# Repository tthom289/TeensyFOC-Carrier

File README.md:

# TeensyFOC-Carrier

Teensy 4.0 + SimpleFOC carrier board for brushless motor control in a rotating LiDAR SLAM platform. Designed for the [Subterranean Systems](https://youtube.com/@subterraneansystems) VLP-16 scanner — integrates AS5600 magnetic encoder, slip ring passthrough, and GT2 belt drive motor driver circuitry on a compact custom PCB.

---

## Overview

This board eliminates the wiring mess of a breadboarded SimpleFOC setup by consolidating the Teensy 4.0, motor driver interface, and encoder connections onto a single PCB. Designed specifically for the rotating LiDAR scanner in the Subterranean Systems cave mapping platform.

**Key features:**
- Teensy 4.0 footprint with all relevant I/O broken out
- SimpleFOC-compatible motor driver header
- AS5600 magnetic encoder interface (I2C)
- JST-XHP connectors for motor phase and power leads
- Slip ring wiring passthrough support
- Designed in KiCad

---

## Bill of Materials (Connectors)

| Component | Link |
|---|---|
| Single Row 2.54mm Headers | [Amazon](https://amzn.to/3Nf74dT) |
| JST-XHP Connector Kit | [Amazon](https://amzn.to/4dmR5oD) |

---

## Related

- [Subterranean Systems YouTube](https://youtube.com/9nl) — build videos for this platform
- [SimpleFOC](https://simplefoc.com/) — motor control library

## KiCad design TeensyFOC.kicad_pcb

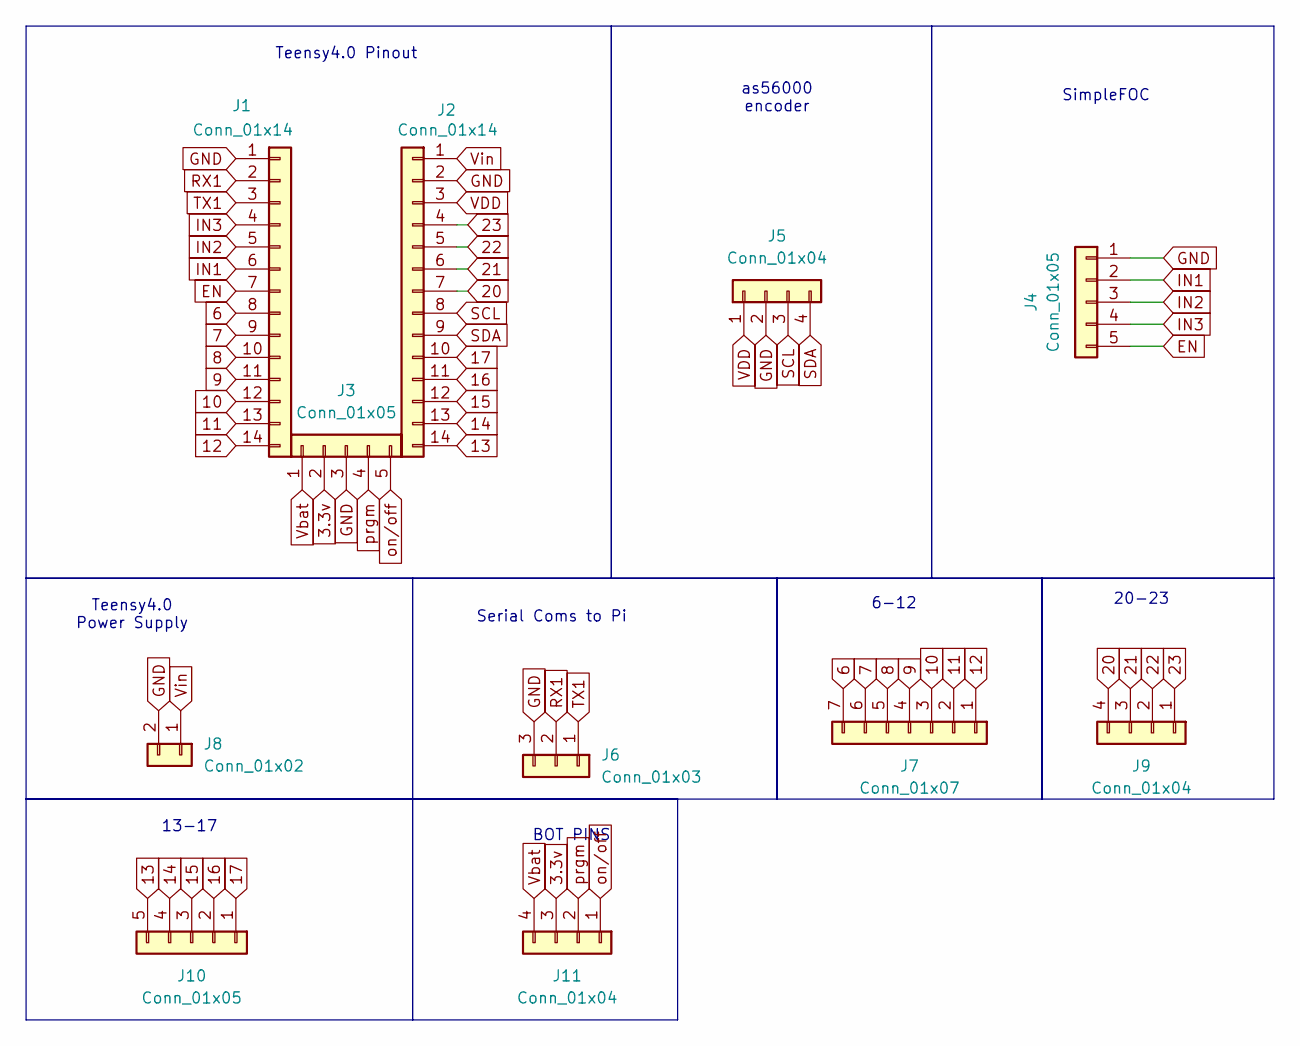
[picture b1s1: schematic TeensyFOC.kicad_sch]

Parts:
J1, J2: Conn_01x14; PinSocket_1x14_P2.54mm_Vertical
J3, J4, J10: Conn_01x05; PinSocket_1x05_P2.54mm_Vertical
J5: Conn_01x04; JST_XH_B4B-XH-A_1x04_P2.50mm_Vertical
J6: Conn_01x03; JST_XH_B3B-XH-A_1x03_P2.50mm_Vertical
J7: Conn_01x07; PinSocket_1x07_P2.54mm_Vertical
J8: Conn_01x02; JST_XH_B2B-XH-A_1x02_P2.50mm_Vertical
J9, J11: Conn_01x04; PinSocket_1x04_P2.54mm_Vertical

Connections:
3.3v: J3.2, J11.3
6: J1.8, J7.7
7: J1.9, J7.6
8: J1.10, J7.5
9: J1.11, J7.4
10: J1.12, J7.3
11: J1.13, J7.2
12: J1.14, J7.1
13: J2.14, J10.5
14: J2.13, J10.4
15: J2.12, J10.3
16: J2.11, J10.2
17: J2.10, J10.1
20: J2.7, J9.4
21: J2.6, J9.3
22: J2.5, J9.2
23: J2.4, J9.1
EN: J1.7, J4.5
GND: J1.1, J2.2, J3.3, J4.1, J5.2, J6.3, J8.2
IN1: J1.6, J4.2
IN2: J1.5, J4.3
IN3: J1.4, J4.4
RX1: J1.2, J6.2
SCL: J2.8, J5.3
SDA: J2.9, J5.4
TX1: J1.3, J6.1
VDD: J2.3, J5.1
Vbat: J3.1, J11.4
Vin: J2.1, J8.1
on/off: J3.5, J11.1
prgm: J3.4, J11.2

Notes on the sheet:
Teensy4.0 Pinout
13-17
20-23
6-12
Serial Coms to Pi
Teensy4.0 Power Supply
BOT PINS
SimpleFOC
as56000 encoder

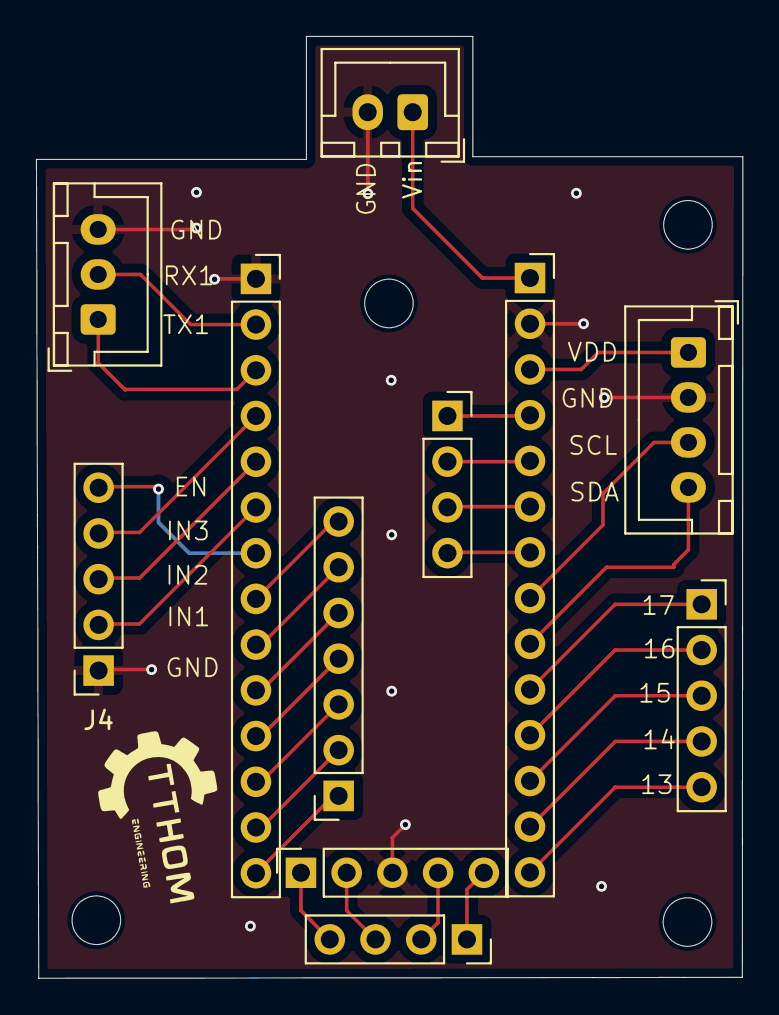
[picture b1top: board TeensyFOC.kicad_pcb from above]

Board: 2 copper layers, 39.2 x 52.3 mm, 11 parts (0 on the bottom side), 31 nets.

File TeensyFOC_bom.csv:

Designator,Footprint,Quantity,Value,LCSC Part #
"J1, J2",PinSocket_1x14_P2.54mm_Vertical,2,Conn_01x14,
"J10, J3",PinSocket_1x05_P2.54mm_Vertical,2,Conn_01x05,
"J11, J9",PinSocket_1x04_P2.54mm_Vertical,2,Conn_01x04,
J4,JST_XH_B5B-XH-A_1x05_P2.50mm_Vertical,1,Conn_01x05,
J5,JST_XH_B4B-XH-A_1x04_P2.50mm_Vertical,1,Conn_01x04,
J6,JST_XH_B3B-XH-A_1x03_P2.50mm_Vertical,1,Conn_01x03,
J7,PinSocket_1x07_P2.54mm_Vertical,1,Conn_01x07,
J8,JST_XH_B2B-XH-A_1x02_P2.50mm_Vertical,1,Conn_01x02,

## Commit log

2026-03-15 Enhance README with overview and features
    Added detailed overview, key features, bill of materials, and related links for the TeensyFOC-Carrier.
2026-03-17 Add MIT License to the project
